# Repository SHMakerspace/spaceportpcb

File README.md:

Spaceport PCBs
============
This repos is the 2 PCBs which make up the client portion of [Spaceport](https://github.com/SHMakerspace/spaceport). This consists of the **Spaceport Controller** and the **Spaceport reader**.

Design has been created in EagleCAD.

![PCBs](https://lh3.googleusercontent.com/g8-eCmGsM58siEUREAJQxgl26oSliJ-2NyPW6FOMdzvt_YHkEdBsc1cU5JWBC_lprGO7F8F3ThcDM_IRJHGNp3lH1DRBhw5yG0vpXb5wSVXzZ42BomTwUZnGATMCjlY0k3_H5Yt0mAFraEeLzEeb6mTGwxtiBvsvU_cfevI-thxgwVujKMEgD9XBA_XJLVQzAwf8d0RPYAYVQGPrfWlY_laGTWThU_avMRDu92ImBItWaK0IjaGnYVnYxnggVs4SwaaNuJpahqiSyLMhoGB9ldxzHuoans6Ikqi9QLDSBORbWw5_zX3XY1whjGAgJjJJpDNsrc3af8auh3d60lcXBpei0LkKFs6z0Sxrel0nS1Bge0rzmwRRYahMxtU5Eh58kv9pTjtxhfeFLGm6uNuZOdXpnKjWtL1RWKSHmZ5YliH4tDq5j5zixpuK-VZTfNrQDeJjGsRYbCt8ifrUpd-hSE3mDRIExDh6mEqFzbzMBJwEUJ4LLboPXsA984RTtAiPNChG5fLxXXG1uoGWbgZUuVMKg13lt4O5OBFcVLWfw3khb7lOyGHchTCrdPyaUzFsNmHRzKGXfn6DehrlLwFKzJGggAWy8papKypQXUm6yjXvfaEbS-d9mdQl7Ckjdo1TqbX3iGQynoajx5urhemQ9bXHlX8NNMWd=w1257-h711-no)

Instructions and more information on Spaceport can be found in the [Spaceport repo](https://github.com/SHMakerspace/spaceport).

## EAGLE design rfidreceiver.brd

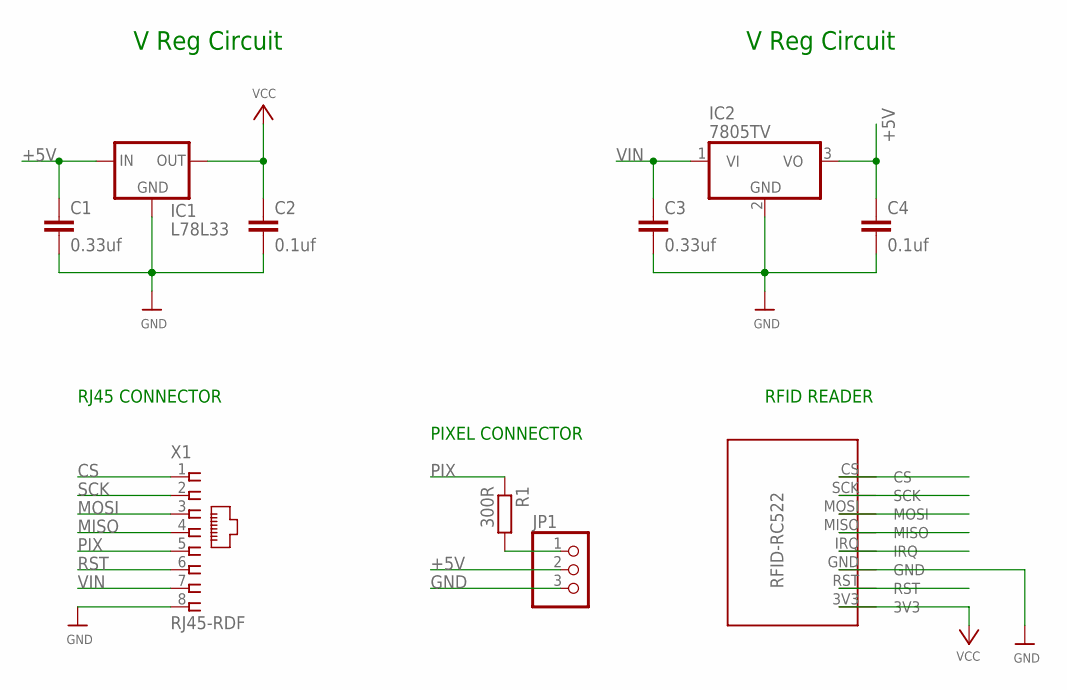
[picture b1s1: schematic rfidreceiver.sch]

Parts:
C1, C3: 0.33uf; C050-024X044
C2, C4: 0.1uf; C050-024X044
IC1: L78L33; TO92-INLINE
IC2: 7805TV; TO220V
JP1: PINHD-1X3CB; 1X03-CLEANBIG
R1: 300R; 0204/5
U$2: RFID-RC522
X1: RJ45-RDF

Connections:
+5V: C1.1, C4.1, IC1.1 (IN), IC2.3 (VO), JP1.2
CS: U$2.CS, X1.1
GND: C1.2, C2.2, C3.2, C4.2, IC1.2 (GND), IC2.2 (GND), JP1.3, U$2.GND, X1.8
IRQ: U$2.IRQ
MISO: U$2.MISO, X1.4
MOSI: U$2.MOSI, X1.3
unnamed: JP1.1, R1.2
PIX: R1.1, X1.5
RST: U$2.RST, X1.6
SCK: U$2.SCK, X1.2
VCC: C2.1, IC1.3 (OUT), U$2.3V3
VIN: C3.1, IC2.1 (VI), X1.7

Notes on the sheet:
V Reg Circuit
PIXEL CONNECTOR
RFID READER
RJ45 CONNECTOR

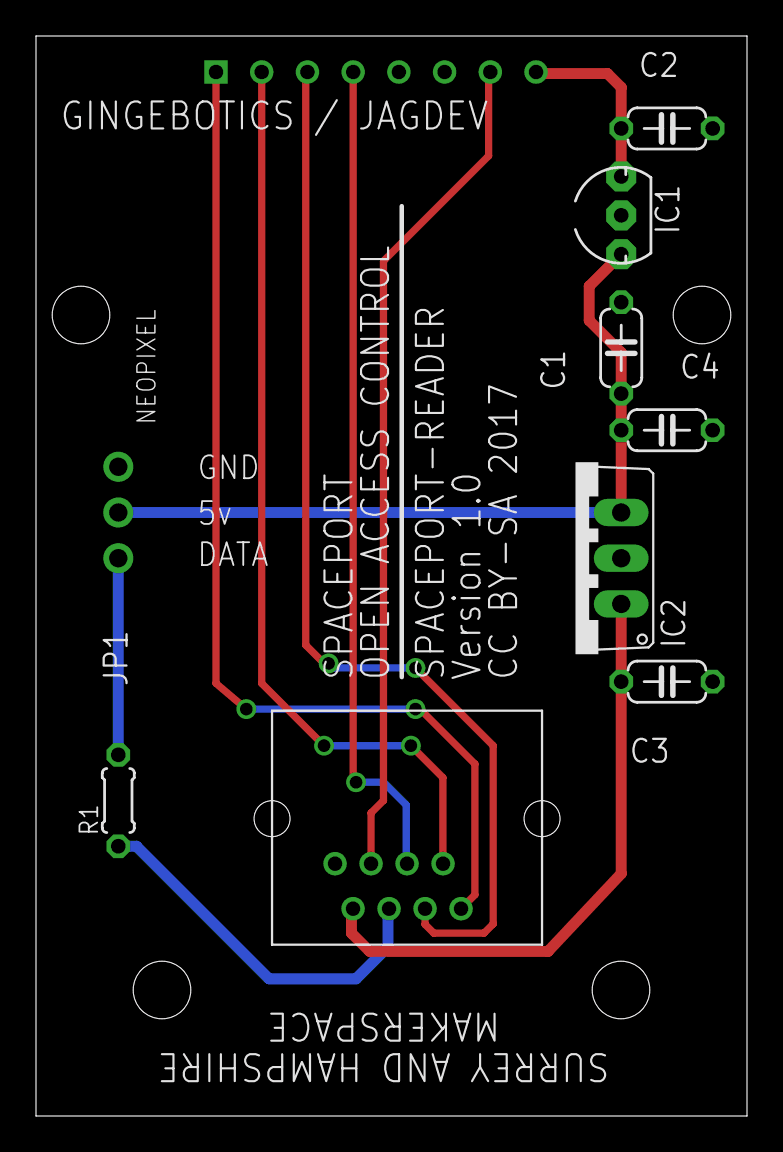
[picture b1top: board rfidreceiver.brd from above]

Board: 2 copper layers, 39.5 x 60.0 mm, 10 parts (1 on the bottom side), 11 nets.

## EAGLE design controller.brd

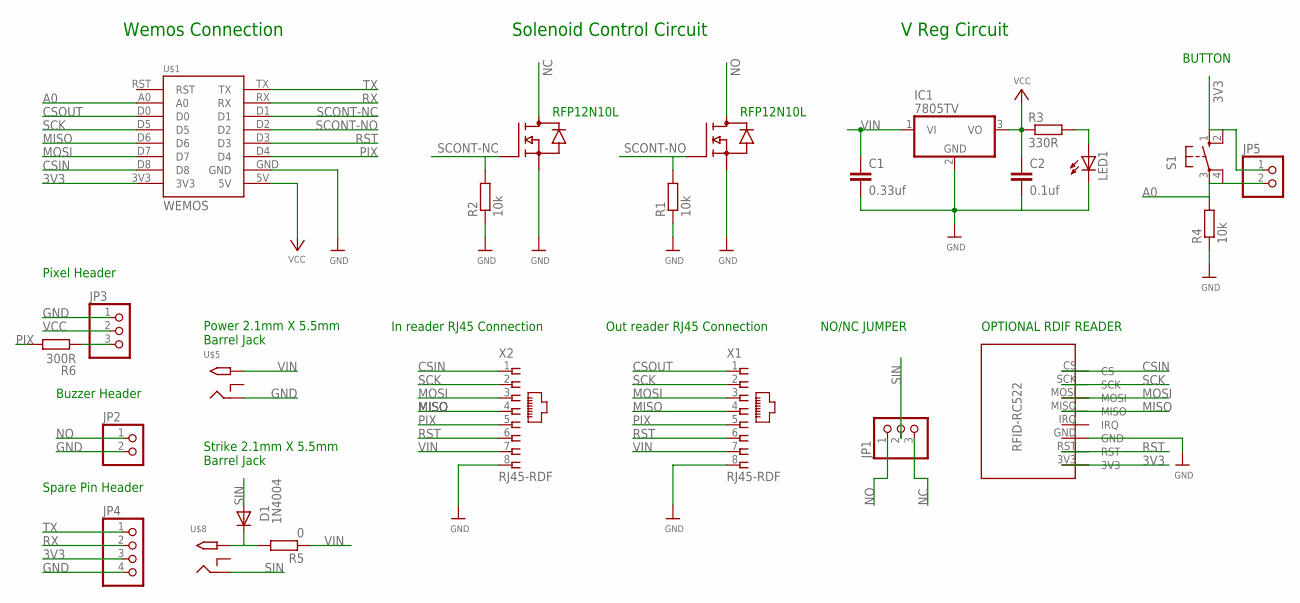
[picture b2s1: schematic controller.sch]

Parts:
C1: 0.33uf; C050-024X044
C2: 0.1uf; C050-024X044
D1: 1N4004; DO41-10
IC1: 7805TV; TO220V
IC2, IC3: NTD4963NT0220; T0220
JP1, JP3: PINHD-1X3CB; 1X03-CLEANBIG
JP2, JP5: PINHD-1X2; 1X02
JP4: PINHD-1X4; 1X04
LED1: LED3MM
R1, R2, R4: 10k; 0204/5
R3: 330R; 0204/5
R5: 0; 0204/5
R6: 300R; 0204/5
S1: 10-XX; B3F-10XX
U$1: WEMOS
U$5, U$8: 2.1MMJACKTHM; PJ-102A
U$14: RFID-RC522NOHOLES; RFID-RC522-NOHOLES
X1, X2: RJ45-RDF

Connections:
3V3: JP4.3, JP5.1, S1.1 (S), S1.2 (S1), U$1.3V3, U$14.3V3
A0: JP5.2, R4.2, S1.3, S1.4 (P1), U$1.A0
CSIN: U$1.D8, U$14.CS, X2.1
CSOUT: U$1.D0, X1.1
GND: C1.2, C2.2, IC1.2 (GND), IC2.3 (S), IC3.3 (S), JP2.2, JP3.1, JP4.4, LED1.K (C), R1.1, R2.1, R4.1, U$1.GND, U$5.RING, X1.8, X2.8
MISO: U$1.D6, U$14.MISO, X1.4, X2.4
MOSI: U$1.D7, U$14.MOSI, X1.3, X2.3
unnamed: D1.C, R5.2, U$8.TIP
unnamed: JP3.3, R6.1
unnamed: LED1.A, R3.2
NC: IC2.2 (D), JP1.3
NO: IC3.2 (D), JP1.1, JP2.1
PIX: R6.2, U$1.D4, X1.5, X2.5
RST: U$1.D3, U$14.RST, X1.6, X2.6
RX: JP4.2, U$1.RX
SCK: U$1.D5, U$14.SCK, X1.2, X2.2
SCONT-NC: IC2.1 (G), R2.2, U$1.D1
SCONT-NO: IC3.1 (G), R1.2, U$1.D2
SIN: D1.A, JP1.2, U$8.RING
TX: JP4.1, U$1.TX
VCC: C2.1, IC1.3 (VO), JP3.2, R3.1, U$1.5V
VIN: C1.1, IC1.1 (VI), R5.1, U$5.TIP, X1.7, X2.7

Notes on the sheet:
V Reg Circuit
Wemos Connection
Solenoid Control Circuit
Power 2.1mm X 5.5mm Barrel Jack
In reader RJ45 Connection
Out reader RJ45 Connection
NO/NC JUMPER
Strike 2.1mm X 5.5mm Barrel Jack
Buzzer Header
Spare Pin Header
RFP12N10L
Pixel Header
OPTIONAL RDIF READER
BUTTON

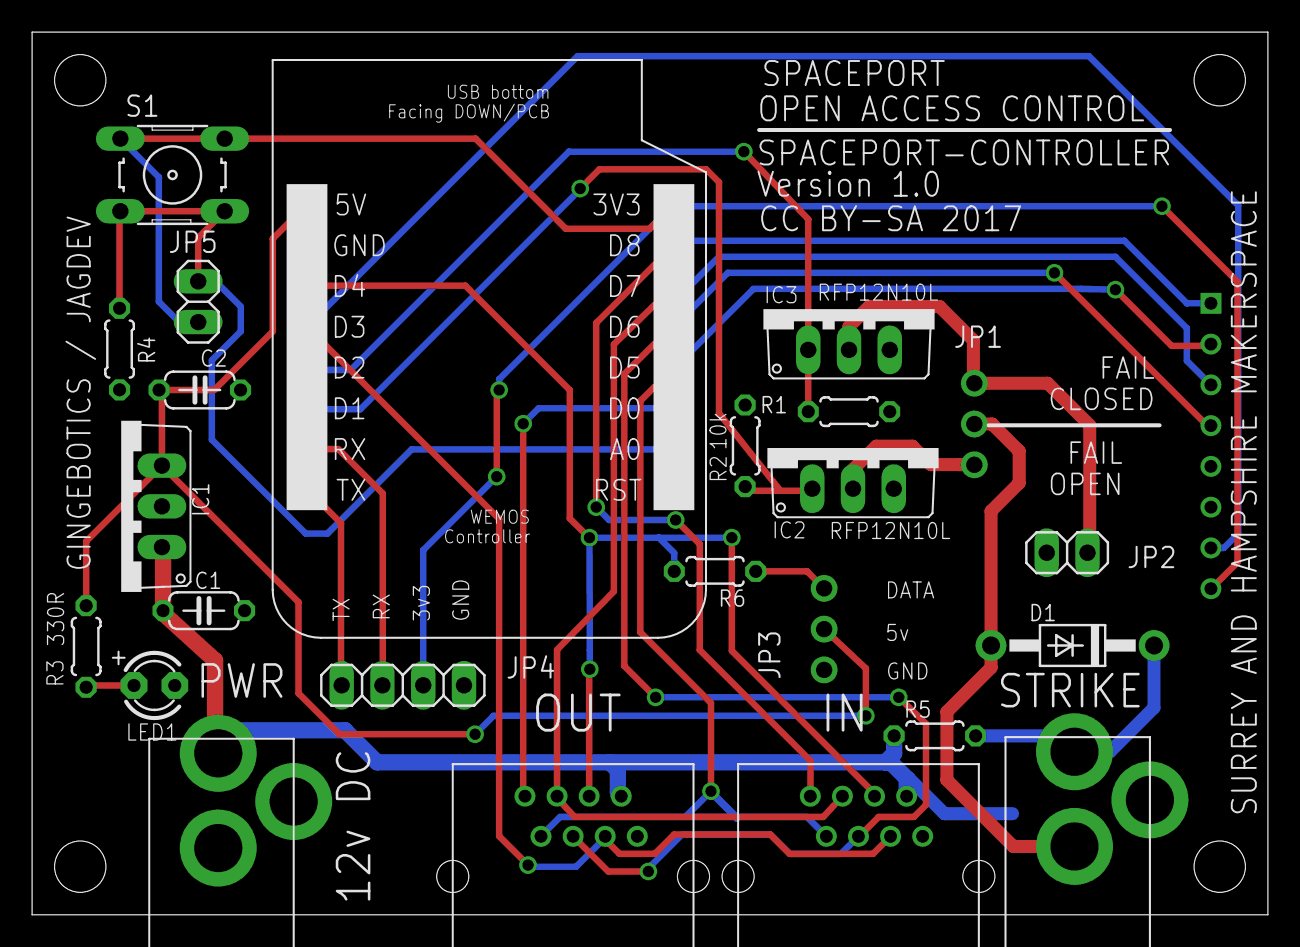
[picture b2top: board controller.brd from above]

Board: 2 copper layers, 77.0 x 55.0 mm, 25 parts (1 on the bottom side), 22 nets.

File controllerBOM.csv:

"Qty";"Value";"Device";"Package";"Parts";"Description";"MF";"MPN";"OC_FARNELL";"OC_NEWARK";
"1";"";"10-XX";"B3F-10XX";"S1";"OMRON SWITCH";"";"B3F-1000";"176432";"36M3542";
"1";"";"LED3MM";"LED3MM";"LED1";"LED";"";"";"";"";
"2";"";"PINHD-1X2";"1X02";"JP2, JP5";"PIN HEADER";"";"";"";"";
"2";"";"PINHD-1X3CB";"1X03-CLEANBIG";"JP1, JP3";"PIN HEADER";"";"";"";"";
"1";"";"PINHD-1X4";"1X04";"JP4";"PIN HEADER";"";"";"";"";
"1";"0";"R-EU_0204/5";"0204/5";"R5";"RESISTOR, European symbol";"";"";"";"";
"1";"0.1uf";"C-EU050-024X044";"C050-024X044";"C2";"CAPACITOR, European symbol";"";"";"";"";
"1";"0.33uf";"C-EU050-024X044";"C050-024X044";"C1";"CAPACITOR, European symbol";"";"";"";"";
"3";"10k";"R-EU_0204/5";"0204/5";"R1, R2, R4";"RESISTOR, European symbol";"";"";"";"";
"1";"1N4004";"1N4004";"DO41-10";"D1";"DIODE";"";"";"";"";
"2";"2.1MMJACKTHM";"2.1MMJACKTHM";"PJ-102A";"U$5, U$8";"2.1mm x 5.5mm THM DC jack with internal switch. Digikey part #PJ-102A, 4UCON part #05537";"";"";"";"";
"1";"300R";"R-EU_0204/5";"0204/5";"R6";"RESISTOR, European symbol";"";"";"";"";
"1";"330R";"R-EU_0204/5";"0204/5";"R3";"RESISTOR, European symbol";"";"";"";"";
"1";"7805TV";"7805TV";"TO220V";"IC1";"Positive VOLTAGE REGULATOR";"";"";"";"";
"2";"NTD4963NT0220";"NTD4963NT0220";"T0220";"IC2, IC3";"";"";"";"";"";
"1";"RFID-RC522NOHOLES";"RFID-RC522NOHOLES";"RFID-RC522-NOHOLES";"U$14";"";"";"";"";"";
"2";"RJ45-RDF";"RJ45-RDF";"RJ45-RDF";"X1, X2";"";"";"";"";"";
"1";"WEMOS";"WEMOS";"WEMOS";"U$1";"";"";"";"";"";

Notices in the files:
controller.brd:
CC BY-SA 2017
